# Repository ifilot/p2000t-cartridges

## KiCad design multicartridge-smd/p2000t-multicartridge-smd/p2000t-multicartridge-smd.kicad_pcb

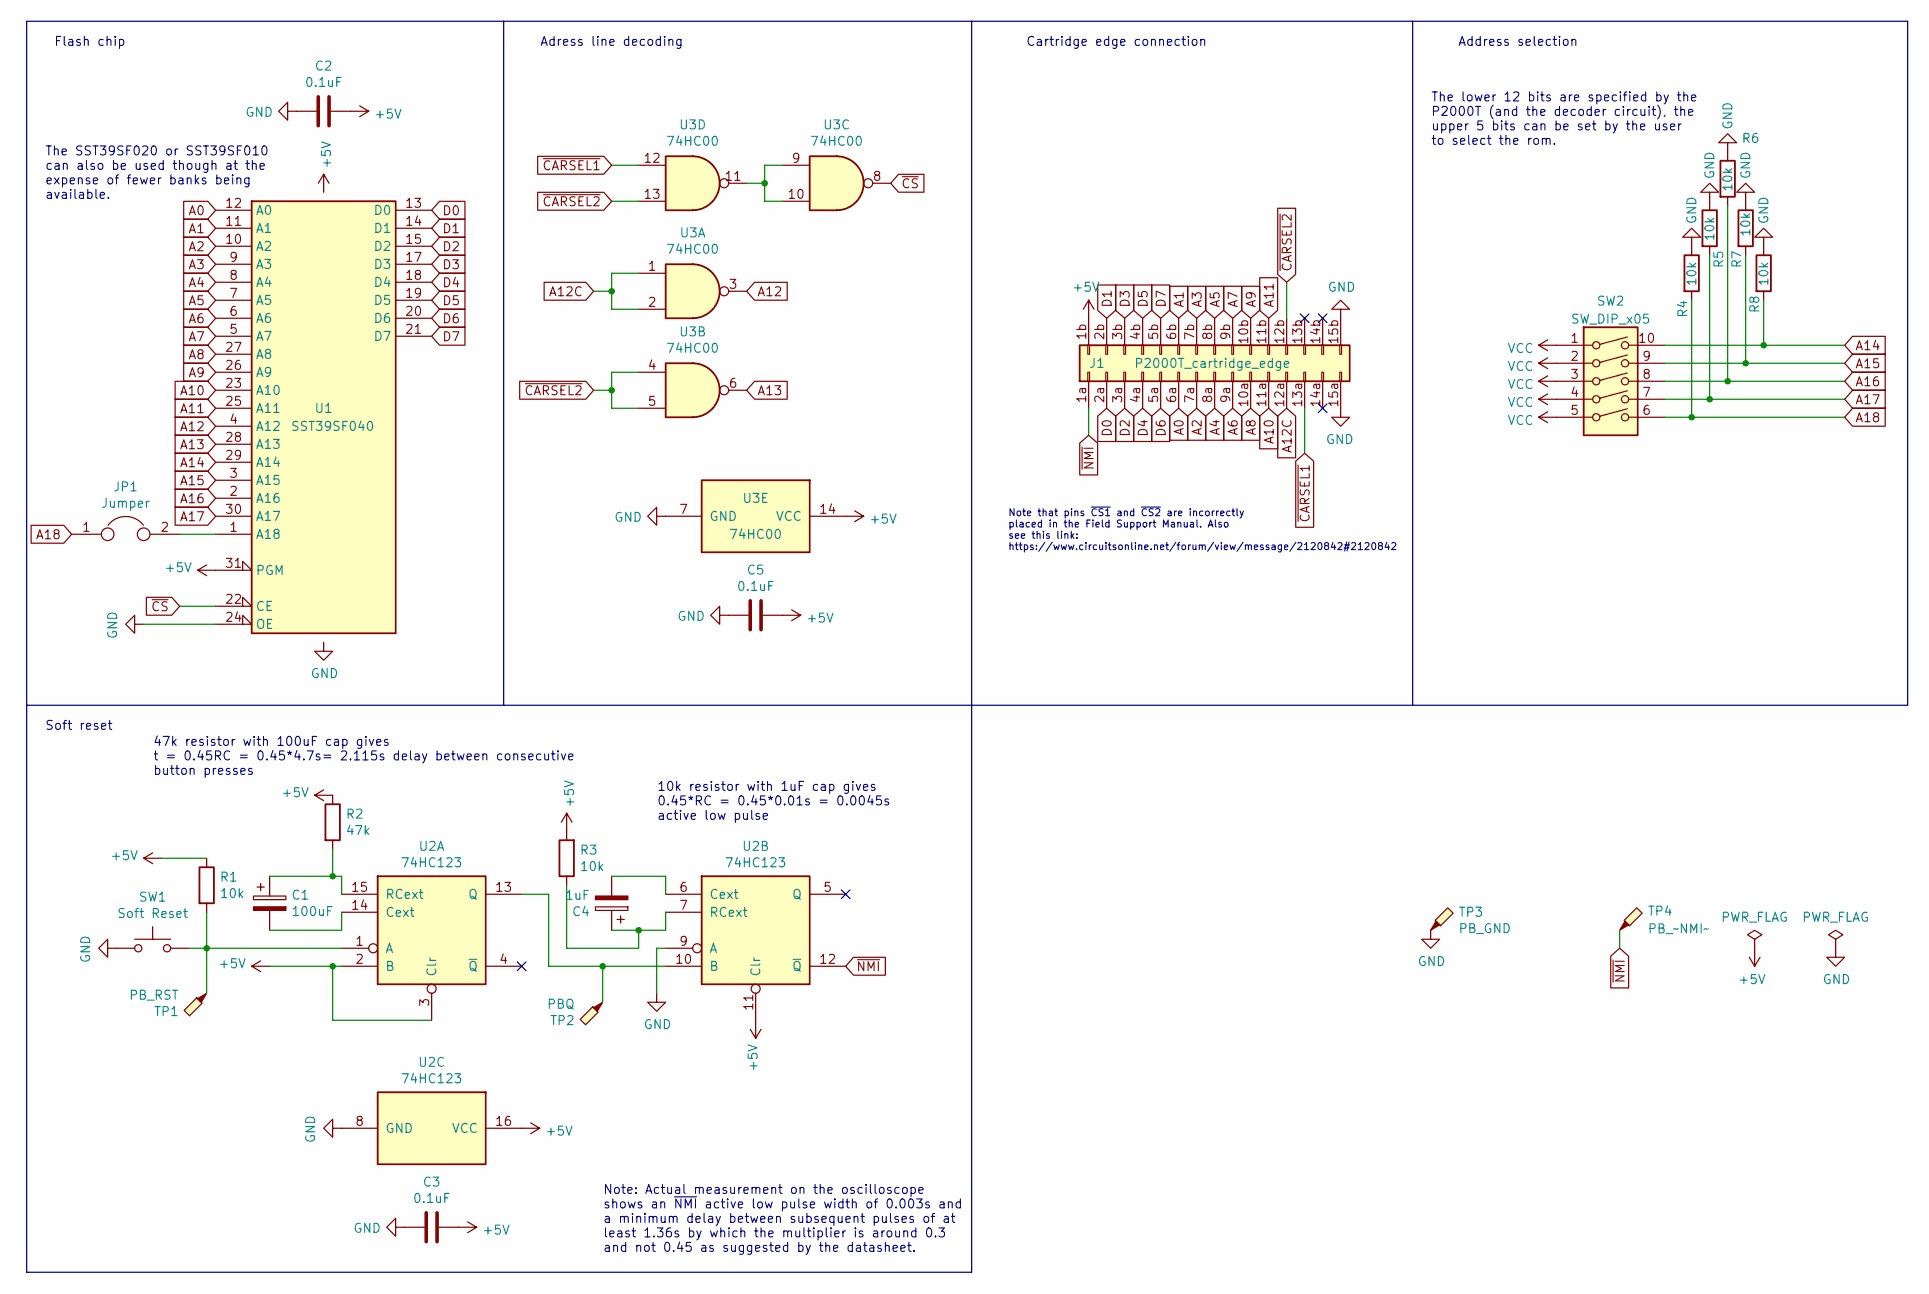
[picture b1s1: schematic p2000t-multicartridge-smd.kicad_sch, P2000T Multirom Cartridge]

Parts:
C1: 100uF; CP_EIA-3528-21_Kemet-B; JLCPCB C16133
C2, C3, C5: 0.1uF; C_0805_2012Metric; JLCPCB C49678
C4: 1uF; C_0805_2012Metric; JLCPCB C28323
J1: P2000T_cartridge_edge; p2000t_cartridge_edge
JP1: Jumper; SolderJumper-2_P1.3mm_Open_TrianglePad1.0x1.5mm
R1, R3, R4, R5, R6, R7, R8: 10k; R_0805_2012Metric; JLCPCB C17414
R2: 47k; R_0805_2012Metric; JLCPCB C17713
SW1: Soft Reset; SW_PUSH_6mm
SW2: SW_DIP_x05; SW_DIP_SPSTx05_Slide_9.78x14.88mm_W7.62mm_P2.54mm
TP1: PB_RST; TestPoint_THTPad_D1.5mm_Drill0.7mm
TP2: PBQ; TestPoint_THTPad_D1.5mm_Drill0.7mm
TP3: PB_GND; TestPoint_THTPad_D1.5mm_Drill0.7mm
TP4: PB_~NMI~; TestPoint_THTPad_D1.5mm_Drill0.7mm
U1: SST39SF040; PLCC-32_THT-Socket
U2: 74HC123; SOIC-16_3.9x9.9mm_P1.27mm
U3: 74HC00; SOIC-14_3.9x8.7mm_P1.27mm

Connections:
A0: J1.6a, U1.12 (A0)
A1: J1.6b, U1.11 (A1)
A2: J1.7a, U1.10 (A2)
A3: J1.7b, U1.9 (A3)
A4: J1.8a, U1.8 (A4)
A5: J1.8b, U1.7 (A5)
A6: J1.9a, U1.6 (A6)
A7: J1.9b, U1.5 (A7)
A8: J1.10a, U1.27 (A8)
A9: J1.10b, U1.26 (A9)
A10: J1.11a, U1.23 (A10)
A11: J1.11b, U1.25 (A11)
A12: U1.4 (A12), U3.3
A12C: J1.12a, U3.1, U3.2
A13: U1.28 (A13), U3.6
A14: R8.2, SW2.10, U1.29 (A14)
A15: R7.2, SW2.9, U1.3 (A15)
A16: R6.2, SW2.8, U1.2 (A16)
A17: R5.2, SW2.7, U1.30 (A17)
A18: JP1.1, R4.2, SW2.6
D0: J1.2a, U1.13 (D0)
D1: J1.2b, U1.14 (D1)
D2: J1.3a, U1.15 (D2)
D3: J1.3b, U1.17 (D3)
D4: J1.4a, U1.18 (D4)
D5: J1.4b, U1.19 (D5)
D6: J1.5a, U1.20 (D6)
D7: J1.5b, U1.21 (D7)
GND: C2.2, C3.2, C5.2, J1.15a, J1.15b, R4.1, R5.1, R6.1, R7.1, R8.1, SW1.1, TP3.1, U1.16 (GND), U1.24 (OE), U2.8 (GND), U2.9 (A), U3.7 (GND)
unnamed: C1.1, R2.2, U2.15 (RCext)
unnamed: C1.2, U2.14 (Cext)
unnamed: C4.1, R3.1, U2.7 (RCext)
unnamed: C4.2, U2.6 (Cext)
unnamed: JP1.2, U1.1 (A18)
unnamed: R1.2, SW1.2, TP1.1, U2.1 (A)
unnamed: TP2.1, U2.10 (B), U2.13 (Q)
unnamed: U3.9, U3.10, U3.11
~CARSEL1: J1.13a, U3.12
~CARSEL2: J1.12b, U3.4, U3.5, U3.13
~CS: U1.22 (CE), U3.8
~NMI: J1.1a, TP4.1, U2.12 (~Q)

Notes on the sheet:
Note that pins ~{CS1} and ~{CS2} are incorrectly placed in the Field Support Manual. Also see this link: https://www.circuitsonline.net/forum/view/message/2120842#2120842
Note: Actual measurement on the oscilloscope shows an ~{NMI} active low pulse width of 0.003s and a minimum delay between subsequent pulses of at least 1.36s by which the multiplier is around 0.3 and not 0.45 as suggested by the datasheet.
Cartridge edge connection
Flash chip
Adress line decoding
The SST39SF020 or SST39SF010 can also be used though at the expense of fewer banks being available.
Soft reset
47k resistor with 100uF cap gives t = 0.45RC = 0.45*4.7s= 2.115s delay between consecutive button presses
10k resistor with 1uF cap gives 0.45*RC = 0.45*0.01s = 0.0045s active low pulse
The lower 12 bits are specified by the P2000T (and the decoder circuit), the upper 5 bits can be set by the user to select the rom.
Address selection

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
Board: 2 copper layers, 24 parts (18 on the bottom side), 42 nets, no tracks yet.
